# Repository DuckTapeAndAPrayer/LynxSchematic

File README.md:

# Lynx HIB (Hardware Interface Board) Schematic
This repo contains a reverse engineered schematic of and info on the Lynx HIB (REV Robotics Expansion Hub, and the Expansion Hub part of the Control Hub). This was done with a multimeter; it may have some errors.

The schematic itself is in the `pcb` directory. Photos can be found in the `photos` directory. Notes on repairs can be found in the `repair notes` directory

## PCB versions
This schematic was created from a revision 2.3 Lynx HIB. This revision uses a Bosch BNO055 IMU and still includes an IMU in Expansion Hubs. Control Hubs and Expansion Hubs of this revision only differ by the inclusion of a compute board. Newer Control Hubs (sold after September 2022) seem to use a revision 2.4c or 2.5 HIB and have an Bosch BHI260AP IMU. The IMU section of the schematic has both in revisions's in it. Other sections seem to be the same aside from some component supplier changes and some additional zero ohm resistors around the compute board header. These zero ohm resistors aren't included in the schematic. I have not seen inside an Expansion Hub without an IMU (those sold after December 1, 2021), so I don't know how accurate this schematic is for them and how were changed from revision 2.3.

### References
- [Expansion Hub IMU Removal Notice](https://www.revrobotics.com/blog/expansion-hub-IMU-updates)
- [Control Hub and IMU differences](https://docs.revrobotics.com/duo-control/sensors/i2c/imu)

## Firmware

### MCU
The MCU firmware can be found on [REV's website](https://docs.revrobotics.com/duo-control/managing-the-control-system/updating-firmware/firmware-changelog).

#### Notes on replacing the MCU
- Use lots of flux for each step
- Use a pre-heater or heated plate to preheat the board for removal and replacement. The amount of copper on the board makes the MCU hard to work on otherwise
- Use hot air to remove the MCU. Even a cheap hot air gun without temperature control will work
- Try not to overheat the MCU while soldering
- Check the 3.3V rail for shorts by measuring the resistance across C63. If there are any at this point there are other problems on your board
- Tack in the corners of the new chip and drag solder the rest of the pins
- Once soldered in, do a visual inspection for poor solder joints or shorts between pins
- Next, check the 3.3V rail for shorts again. <!-- CHECK: It should be over 100 ohms. --> If there are any shorts the inspect the pins again and reflow and problem area.
- Apply power to the board and check if the 3.3v rail has come up to 3.3v
- Check that there is 1.2v across C28, C30, or C34 to check that the core voltage rail has come up. If not try to reflow the pins again.

#### First Upload
The first upload must be done with a debugger.

A method for uploading follows:
1) If your HIB's revision is > 2.3, solder on a JTAG connector or some leads
2) Acquire a "FTDI FT2232H Mini Module" to use as a JTAG debug probe. A genuine one from FTDI has a better chance of working reliably. Alternatively, use an ST-Link from STMicroelectronics. An ST-Link v2 was tested but a V1 should also work, but it may need a config change.
3) Connect the Mini Module or ST-Link to the HIB. They can be cleanly connected by making an adapter out of some 0.1" pitch header and half of a pre terminated cable sold by Molex that connects to the HIB's JTAG connector. See below for the cable's part number. The pinout of the JTAG connector can be found in the schematic. Connect  
    - GND to GND
    - TCK/SWCLK to ADBUS0
    - TDI to ADBUS1
    - TDO to ADBUS2
    - TMS/SWDIO to ADBUS3  
  Or with an ST-Link:
    - GND to GND
    - TCK/SWCLK to SWCLK
    - TMS/SWDIO to SWDIO
4) Download [OpenOCD](https://openocd.org/) or install it from your favorite package manager. This flashing process has been tested with OpenOCD v0.12.0, but newer versions should work
5) Download the config files for the Lynx HIB and Mini Module or ST-Link [here](https://github.com/DuckTapeAndAPrayer/DuckLynx/tree/master/openocd%20configs)
6) Connect battery power to the board
7) Run `openocd -f ftdi_lynx.cfg -c "program <path to firmware file> reset; shutdown"` or for an ST-Link run `openocd -f stlink_lynx.cfg -c "program <path to firmware file> reset; shutdown"`
8) Remove power from the board and reapply it. This allows the bootcfg register programming to take effect

#### Subsequent uploads
If firmware has be uploaded before it can be upgraded the same way or with the bootloader by using [REV Hardware Client](https://ftc-docs.firstinspires.org/en/latest/ftc_sdk/updating/hub_firmware/Updating-Hub-Firmware.html), the [FtcRobotController app](https://ftc-docs.firstinspires.org/en/latest/ftc_sdk/updating/hub_firmware/Updating-Hub-Firmware.html), or [DuckUpdate](https://github.com/DuckTapeAndAPrayer/DuckLynx/tree/master/DuckUpdate). [TI's LMFlashProgrammer](https://www.ti.com/tool/LMFLASHPROGRAMMER) will also work if the MCU is restarted into the bootloader. This can be done with DuckUpdate or with [REV's node-expansion-hub-ftdi](https://github.com/REVrobotics/node-expansion-hub-ftdi).

### FT230XQ
There is no firmware for this device, but it needs to have its config updated. Its config holds the serial number for the HIB, so when writing the same config to many devices be careful to not overwrite the serial number field. As well, it is connected to the reset and bootloader entry pins of the MCU and by default it will drive these pins to ground which will hold the MCU in reset forever. To fix this the CBUS pin modes of need to be changed to GPIO. The easiest way to do this is with [FTDI's FT_Prog](https://ftdichip.com/utilities/) utility, but it also can be done with [libftdi](https://www.intra2net.com/en/developer/libftdi/index.php) or [FTDI's d2xx](https://ftdichip.com/drivers/d2xx-drivers/) library. To update the modes with FT_Prog, connect the device to a computer running the program, edit `Hardware Specific` -> `CBUS Signals` to all be `GPIO`, and save the new config to the device.

### BNO055 IMU
The BNO055 IMU has built in firmware from Bosch. It can be updated, but it isn't intended to be replaced by user firmware. If the IMU has to be replaced whatever firmware that ships on the IMU from the factory will be fine. 

### BHI260AP IMU
The BHI260AP IMU has some built in libraries and a bootloader stored in ROM, but the user has to supply firmware. It is either supplied by the host device or it is read from an external SPI flash. On the Lynx HIB an external W25Q64JWSSIQ SPI Flash is used. The flash contains the same data across devices, so it probably doesn't have any device specific calibration in it and if the flash has to be replaced the data from one HIB's flash can be copied to another's

## Components
- A large chunk of the passives are in a 0603 package
- Aux Shunt resistors are 20 mΩ (milliohm) in a 2512 package. P/N - Panasonic ERJ-M1WSF20MU

### ICs
| Description | Part Number | Additional Info |
| ----------- | ----------- | -------- |
| Main MCU | Texas Instruments TM4C123GH6PGEI | 
| Motor controller | STMicroelectronics VNH5050AE |
| USB to UART | FTDI FT230XQ |
| RS485 transceiver | STMicroelectronics ST3485EB |
| Compute board bus transceiver | Texas Instruments SN74LVC8T245 |
| Op Amp for shunts | STMicroelectronics LMV321RILT | For AUX Shunts. Labeled K176. SOT 23-5 |
| 5V Buck converter driver | Texas Instruments TPS54527 | 
| 3.3V Buck converter driver | Texas Instruments TPS562209 |
| Adjustable shunt voltage regulator | Diodes Incorporated TL431ASA | For AREF. U17. labeled AAXXX |
| High side current monitor | Diodes Incorporated ZXCT1010E5TA | U25 |
| USB OTG ESD Diodes | Nexperia PUSBM5V5X4-TL | U19 |
| IMU | Bosch BNO055 | Labeled 701. Revision == 2.3 |
| IMU | Bosch BHI260AP | Revisions > 2.3 |
| 1.8V LDO | MCP1700T-1802E/TT | Revisions > 2.3 |
| Geomagnetic Sensor | Bosch BMM150 | Revisions > 2.3 |
| SPI flash | Winbond W25Q64JWSSIQ | Revisions > 2.3. For IMU |

### Diodes
| Description | Part Number | Additional Info |
| ----------- | ----------- | -------- |
| Status LED | Lite-On LTST-G683GEBW | D1 |
| Zener diode | onsemi 1SMB5931BT3G | For motor drives. D4 |
| Tiny ESD diode | Nexperia PESD15VS1UL | D5 |
| ESD protection diode array | Comchip CPDV5-5V0U(-HF?) | Labeled E5U. SOT-353 |
| ESD protection diode array | Comchip CPDV5-3V3UP(-HF?) | Labeled E3V3. SOT-353 |

### Transistors
Many of these have labels with more characters listed, but those parts are date codes.
| Description | Part Number | Additional Info |
| ----------- | ----------- | -------- |
| Big N channel MOSFET | onsemi FDD9409-F085 | Q29. For reverse current protection |
| NPN Transistor | ROHM DTC143XKA | Labeled 43. LED Driver |
| N channel MOSFET | Nexperia BSH103 | Labeled WJ3. Q15, Q19 |
| P channel MOSFET | Toshiba SSM3J328R | Labeled KFH. 5V servo power enable. Q20 |
| P channel MOSFET | Alpha and Omega AO3407A | Labeled X73L. Used throughout the board. Q22, Q23, Q14, Q27 |
| N channel MOSFET | Diodes Incorporated BSS138 | Labeled K38. Q28. Revision == 2.3 |
| N channel MOSFET | onsemi BSS138K | Labeled SK. Q28. Revision > 2.3 |
| N channel MOSFET | onsemi BSS138 | Labeled SS. Q30 & Q31. Only on revision > 2.3 |
| N channel MOSFET | Alpha and Omega AO3434A | Labeled Y4. Different unknown P/N and labeled N3 on revision == 2.3. Used for GPIO and servo ports |

### Connectors
| Description | Part Number | Additional Info |
| ----------- | ----------- | -------- |
| XT30 Male | Amass XT30UPB-M |
| XT30 Female | Amass XT30UPB-F |
| Mini USB B | MUSBS5FBM1RA | This part number exists nowhere on the internet. It is Leoco product series 0850 and P/N 0850BFBD111. The F could be J or K as the gold plating thickness is unknown. TE Connectivity P/N 1734035-1 seems to have the same pad dimensions, so it may work |
| JTAG Connector Female | Molex 53398-0671 | Connector not included on revision > 2.3. Same part should fit on SPI connector |
| JTAG Connector Male Cable | Molex 15134-0605 | Not on Lynx HIB, but helpful for connecting a debugger |
| All shrouded external connectors | JST PH |
| All motor connectors | JST VH |

### Fuses
All from Bel Power? Bel Fuse? They are green.
| Description | Part Number | Additional Info |
| ----------- | ----------- | -------- |
| 2A hold current | 0ZCJ0200FF2C | Labeled b2. Used on servo ports |
| 1.5A hold current | 0ZCH0150FF2E | Labeled bS. Used for USB port |
| 1A hold current | 0ZCJ0100FF2E | Labeled b1. Used for GPIO ports |
| 0.5A hold current | 0ZCK0050FF2E | Labeled bM. Used for I2C, analog, and encoder ports |

### Other
| Description | Part Number | Additional Info |
| ----------- | ----------- | -------- |
| USB Common Mode Choke | ACM-0603-900-T | L2 |

### Mystery Components
- D2 - Different from revision 2.3 to revision > 2.3
- D3 - Maybe ESD Protection Diode LittelFuse SMF17A
- All the capacitors
- L1
- Y2 - 16 MHz main oscillator
- Y1 - revision 2.3 IMU oscillator. 32.768 KHz

## Notes about the board
- The board seems to have more than two layers, so the creation of a schematic by observation wasn't possible.
- Make sure to not touch the 3.3v buck converter circuitry while the board is powered as the voltage reference can be thrown off which makes the 3.3v rail spike above 3.3v and blow stuff up. It's happened ...
- The 5V rail is not always on. The buck converter IC's enable pin is tied to a GPIO on the MCU. It won't enable without an MCU in place with the correct firmware

### Compute board header (J18)
The header that connects to the compute board (if equipped).

Pin numbering:
```
 1 - - 40
 2 - - 39
 3 - - 38
 :     :
 :     :
20 - - 21
```

The pinout of the connector on the compute board can be found on page 16 of the [96Boards CE Specification Version 1.0](https://raw.githubusercontent.com/96boards/documentation/master/Specifications/96Boards-CE-Specification.pdf).
  - The compute board of the Control Hub is based off this specification, see [gm0](https://gm0.org/en/latest/docs/software/adv-control-system/control-system-internals.html#control-hub) for details

### Bus transceivers
A is Compute Board Header - 1.8V  
B is System - 3.3V  
Eight channels

### MCU connections
Overall temp sensor - in MCU  
3.3V voltage sense - doesn't exist

### FTDI FT230XQ
PB1 (Bootconfig enter bootloader) FT230X Pin 11 (CBUS1) and TP3 (NPRG)  
RST FT230X Pin 12 (CBUS0) and TP2 (NRST)  
PJ7 FT230X Pin 5 (CBUS2)  
PK5 FT230X Pin 16 (RTS) and Compute Board Header 36

### Digital GPIO
- GPIOs are set as open drain pins and have pull up resistors  
- Output and input are from the perspective of the lynx  

### Analog GPIO
VCCA and GNDA are just connected to VCC and GND  
VREFA- is connected to GND  
VREFA+ is connected to a circuit that makes 2.994V. This is derived from the TL431A datasheet by using the formula `Vout = Vref * (1 + (R1 / R2))`, which in the case of the HIB is `2.994 = 2.495 * (1 + (2000 / 10000))`

### 5V rail
Voltage monitoring AIN23 (PP0) - Through resistor divider with two 10K resistors to divide voltage by 2.  

### Servo
Servo 5V enable PC6 - Has pull down  

### Battery
Voltage - connected to AIN22 (PP1) via a 1/6 resistor divider with 10K and 2K resistors  
Current - Uses a high side current monitor IC with a 0.003 ohm shunt and 3K Rout resistor into AIN13 (PD2)  

### External oscillator
Called main oscillator by the datasheet  
16 MHz

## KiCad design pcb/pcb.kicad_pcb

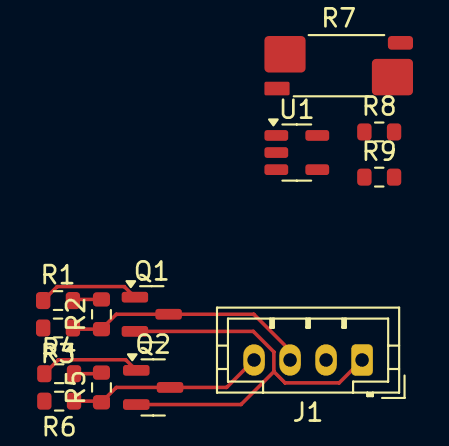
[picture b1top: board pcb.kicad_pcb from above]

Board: 2 copper layers, 13 parts (0 on the bottom side), 10 nets.

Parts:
J1: Conn_01x04_Pin; JST_PH_B4B-PH-K_1x04_P2.00mm_Vertical
Q1, Q2: Q_NMOS; SOT-23
R1, R4: 49K9; R_0603_1608Metric
R2, R5: 10K; R_0603_1608Metric
R3, R6: 4K7; R_0603_1608Metric
R7: R_Shunt; R_Shunt_Vishay_WSK2512_6332Metric_T1.19mm
R8: 29K4; R_0603_1608Metric
R9: 1K; R_0603_1608Metric
U1: LMV321; SOT-23-5

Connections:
/Aux Current Sense/OUT: R8.2, U1.4
/GPIO Module/GPIO Pin1/PIN: J1.4, Q2.3 (D), R5.1, R6.1
/GPIO Module/GPIO Pin2/PIN: J1.3, Q1.3 (D), R2.1, R3.1
/GPIO Module/IN1: Q2.1 (G), R4.1
/GPIO Module/IN2: Q1.1 (G), R1.1
GND: J1.1, Q1.2 (S), Q2.2 (S), R7.4, R9.1
unnamed: R7.2, U1.1 (+)
unnamed: R8.1, R9.2, U1.3 (-)
unnamed: R7.3, U1.2 (V-)
VCC: J1.2, R1.2, R2.2, R4.2, R5.2, U1.5 (V+)

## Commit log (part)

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2026-01-23 Inital Commit
2026-01-23 Fix Formatting
2026-01-25 Grammar
2026-02-10 Update revision information
2026-02-18 Start of repair attempt
2026-03-10 README.md: Various updates/improvements
    - Link to a lot of the datasheets
    - Link to the 96Boards CE Specification for information on the compute board pinout
    - Android board -> Compute board (nothing about the board is Android-specific; it is possible to run regular Linux on it, as described at https://gm0.org/en/latest/docs/software/adv-control-system/co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
    - Various fixes/tweaks
2026-03-12 working microcontroller
2026-03-16 incomplete part 3
2026-03-17 Add more photos and some more documentation
2026-03-17 Updated story & photos
2026-03-17 added test program java files
2026-03-18 added test program config.xml
2026-03-19 typos
2026-03-19 Mihaiberevoescu repair notes edits
2026-03-19 Add new IMU revision and more info in readme
